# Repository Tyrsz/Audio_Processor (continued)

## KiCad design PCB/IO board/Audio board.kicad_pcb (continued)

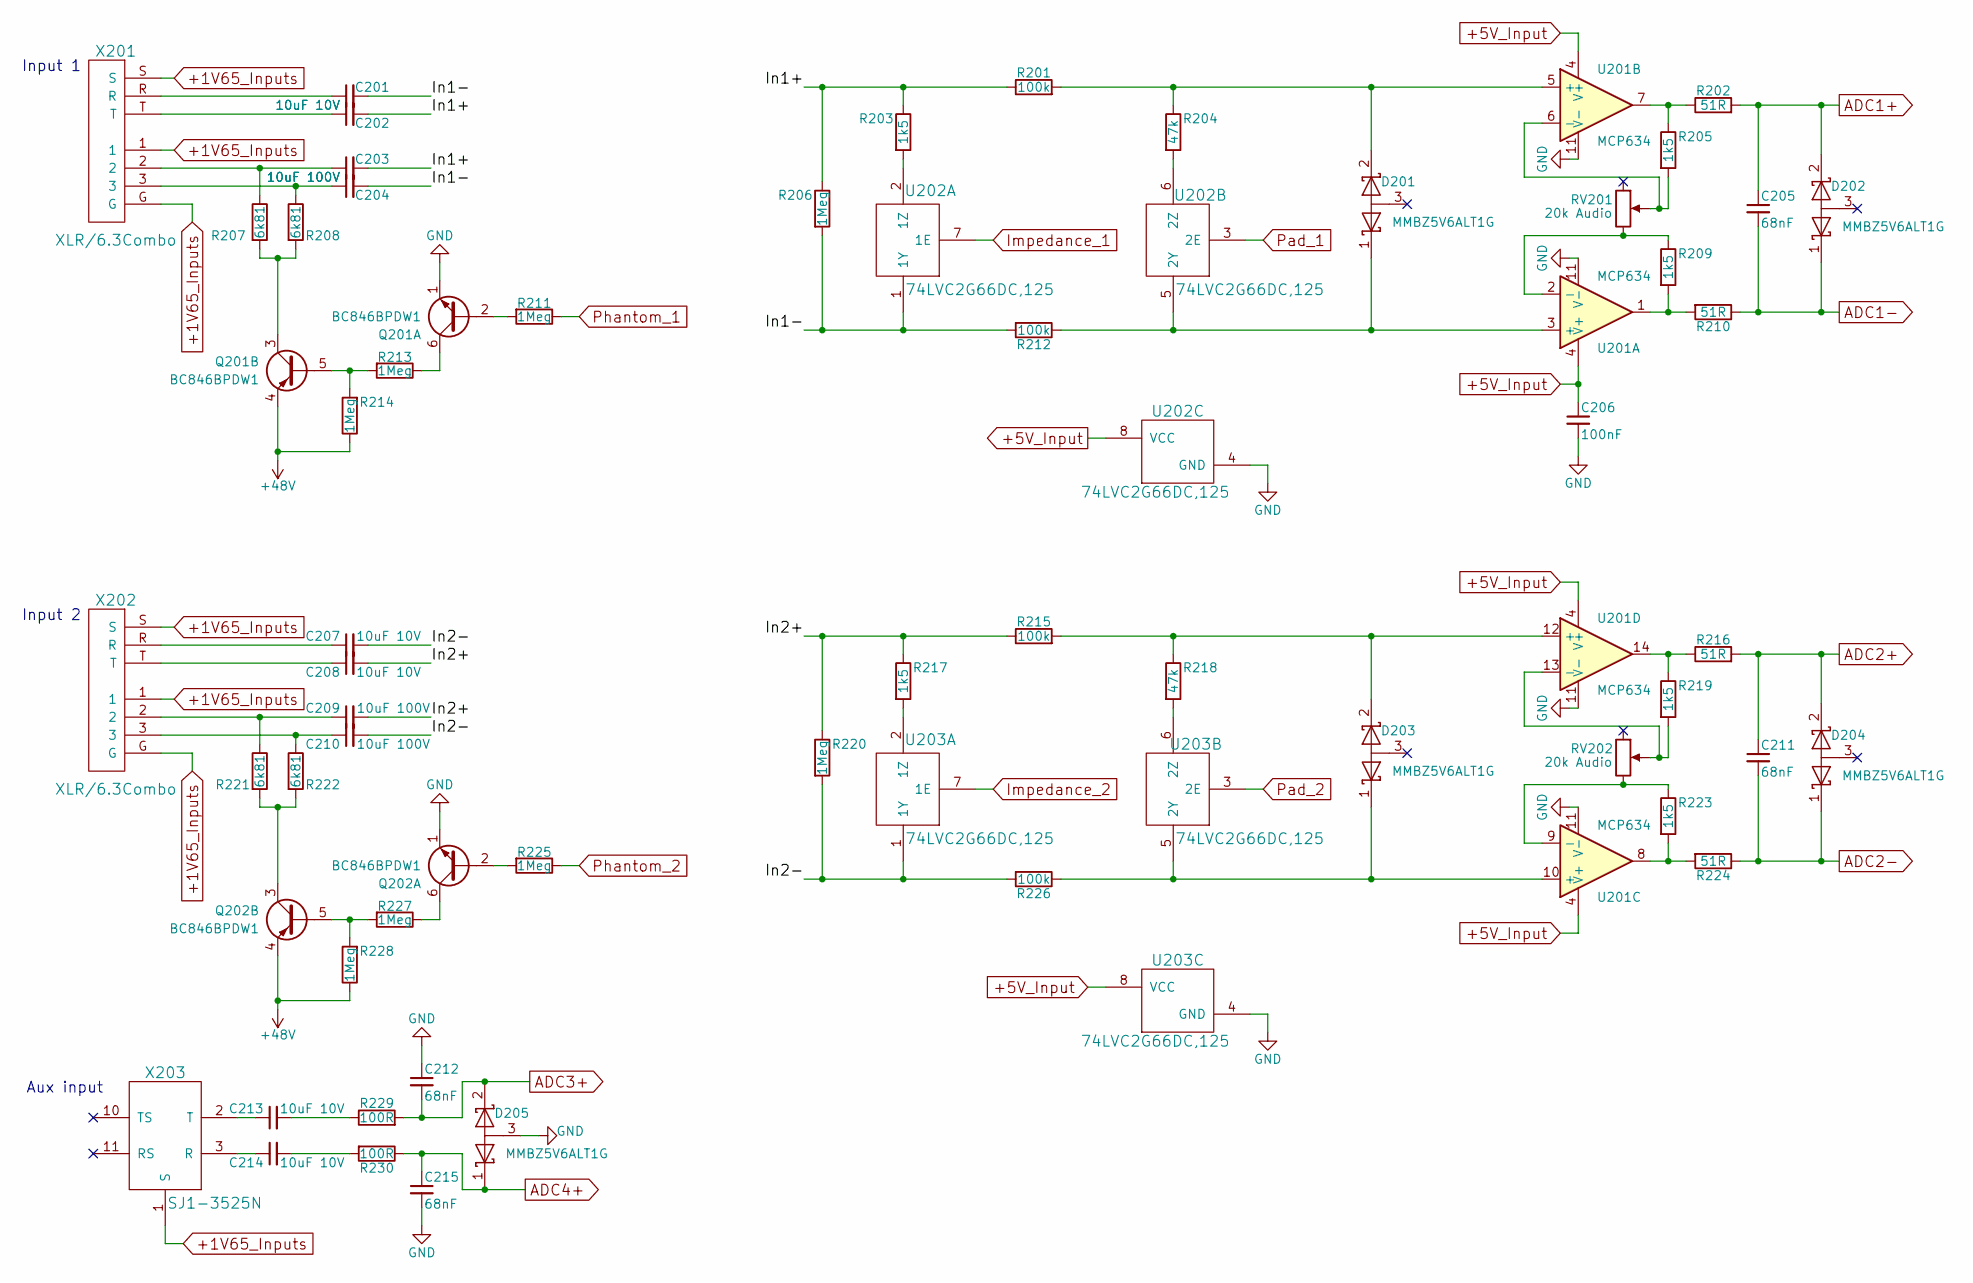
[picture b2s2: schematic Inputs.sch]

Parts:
C201, C202, C207, C208, C213, C214: 10uF 10V; CP_Elec_4x5.3
C203, C204, C209, C210: 10uF 100V; CP_Radial_D8.0mm_P3.50mm
C205, C211, C212, C215: 68nF; C_Rect_L7.5mm_W6.5mm_P5.00mm
C206: 100nF; C_0603
D201, D202, D203, D204, D205: MMBZ5V6ALT1G; SOT-23
Q201, Q202: BC846BPDW1; SOT-363_SC-70-6_Handsoldering
R201, R212, R215, R226: 100k; R_0603
R202, R210, R216, R224: 51R; R_0603
R203, R205, R209, R217, R219, R223: 1k5; R_0603
R204, R218: 47k; R_0603
R206, R211, R213, R214, R220, R225, R227, R228: 1Meg; R_0603
R207, R208, R221, R222: 6k81; R_0603
R229, R230: 100R; R_0603
RV201, RV202: 20k Audio; P140KH1
U201: MCP634; TSSOP-14_4.4x5mm_Pitch0.65mm
U202, U203: 74LVC2G66DC,125; VSSOP-8_2.4x2.1mm_Pitch0.5mm
X201, X202: XLR/6.3Combo; NCJ6FA-H-0
X203: SJ1-3525N; SJ1-352xN

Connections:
+1V65_Inputs: X201.1, X201.G, X201.S, X202.1, X202.G, X202.S, X203.1 (S); also elsewhere on the board
+5V_Input: C206.1, U201.4 (V+), U202.8 (VCC), U203.8 (VCC); also elsewhere on the board
+48V: Q201.4 (E2), Q202.4 (E2), R214.1, R228.1; also elsewhere on the board
/Inputs/In1+: C202.2, C203.2, R201.1, R203.1, R206.1
/Inputs/In1-: C201.2, C204.2, R206.2, R212.2, U202.1 (1Y)
/Inputs/In2+: C208.2, C209.2, R215.1, R217.1, R220.1
/Inputs/In2-: C207.2, C210.2, R220.2, R226.2, U203.1 (1Y)
ADC1+: C205.1, D202.2 (K), R202.2; also elsewhere on the board
ADC1-: C205.2, D202.1 (K), R210.1; also elsewhere on the board
ADC2+: C211.1, D204.2 (K), R216.2; also elsewhere on the board
ADC2-: C211.2, D204.1 (K), R224.1; also elsewhere on the board
ADC3+: C212.2, D205.2 (K), R229.2; also elsewhere on the board
ADC4+: C215.1, D205.1 (K), R230.1; also elsewhere on the board
GND: C206.2, C212.1, C215.2, D205.3 (A), Q201.1 (E1), Q202.1 (E1), U201.11 (V-), U202.4 (GND), U203.4 (GND); also elsewhere on the board
Impedance_1: U202.7 (1E); also elsewhere on the board
Impedance_2: U203.7 (1E); also elsewhere on the board
unnamed: C201.1, X201.R
unnamed: C202.1, X201.T
unnamed: C203.1, R207.1, X201.2
unnamed: C204.1, R208.1, X201.3
unnamed: C207.1, X202.R
unnamed: C208.1, X202.T
unnamed: C209.1, R221.1, X202.2
unnamed: C210.1, R222.1, X202.3
unnamed: C213.1, X203.2 (T)
unnamed: C213.2, R229.1
unnamed: C214.1, X203.3 (R)
unnamed: C214.2, R230.2
unnamed: D201.1 (K), R212.1, U201.3 (+), U202.5 (2Y)
unnamed: D201.2 (K), R201.2, R204.1, U201.5 (+)
unnamed: D203.1 (K), R226.1, U201.10 (+), U203.5 (2Y)
unnamed: D203.2 (K), R215.2, R218.1, U201.12 (+)
unnamed: Q201.2 (B1), R211.2
unnamed: Q201.3 (C2), R207.2, R208.2
unnamed: Q201.5 (B2), R213.2, R214.2
unnamed: Q201.6 (C1), R213.1
unnamed: Q202.2 (B1), R225.2
unnamed: Q202.3 (C2), R221.2, R222.2
unnamed: Q202.5 (B2), R227.2, R228.2
unnamed: Q202.6 (C1), R227.1
unnamed: R202.1, R205.1, U201.7
unnamed: R203.2, U202.2 (1Z)
unnamed: R204.2, U202.6 (2Z)
unnamed: R205.2, RV201.2, U201.6 (-)
unnamed: R209.1, RV201.3, U201.2 (-)
unnamed: R209.2, R210.2, U201.1
unnamed: R216.1, R219.1, U201.14
unnamed: R217.2, U203.2 (1Z)
unnamed: R218.2, U203.6 (2Z)
unnamed: R219.2, RV202.2, U201.13 (-)
unnamed: R223.1, RV202.3, U201.9 (-)
unnamed: R223.2, R224.2, U201.8
Pad_1: U202.3 (2E); also elsewhere on the board
Pad_2: U203.3 (2E); also elsewhere on the board
Phantom_1: R211.1; also elsewhere on the board
Phantom_2: R225.1; also elsewhere on the board

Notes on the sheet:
Aux input
Input 2
Input 1

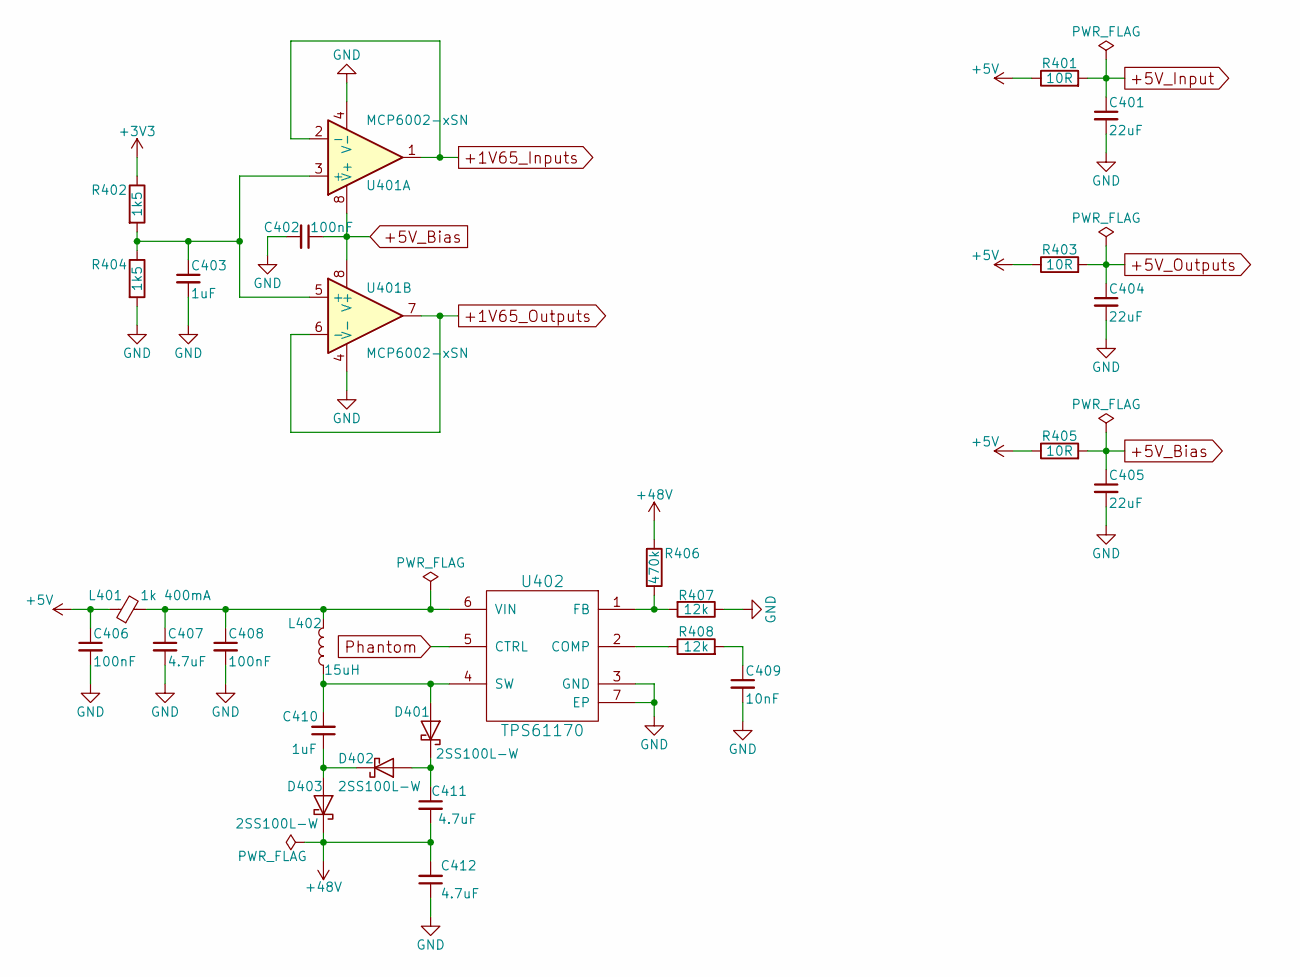
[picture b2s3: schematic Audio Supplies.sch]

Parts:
C401, C404, C405: 22uF; C_0805
C402, C406, C408: 100nF; C_0603
C403: 1uF; C_0603
C407, C411, C412: 4.7uF; C_0805
C409: 10nF; C_0603
C410: 1uF; C_1206
D401, D402, D403: 2SS100L-W; D_SOD-123F
L401: 1k 400mA; L_0603
L402: 15uH; L_0805
R401, R403, R405: 10R; R_0805
R402, R404: 1k5; R_0603
R406: 470k; R_0603
R407, R408: 12k; R_0603
U401: MCP6002-xSN; SOIC-8_3.9x4.9mm_Pitch1.27mm
U402: TPS61170; DFN-6-1EP_2x2mm_Pitch0.65mm

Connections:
+1V65_Inputs: U401.1, U401.2 (-); also elsewhere on the board
+1V65_Outputs: U401.6 (-), U401.7; also elsewhere on the board
+3V3: R402.1; also elsewhere on the board
+5V: C406.1, L401.1, R401.1, R403.1, R405.1; also elsewhere on the board
+5V_Bias: C402.1, C405.1, R405.2, U401.8 (V+)
+5V_Input: C401.1, R401.2; also elsewhere on the board
+5V_Outputs: C404.1, R403.2; also elsewhere on the board
+48V: C411.2, C412.2, D403.1 (K), R406.1; also elsewhere on the board
GND: C401.2, C402.2, C403.2, C404.2, C405.2, C406.2, C407.2, C408.2, C409.2, C412.1, R404.2, R407.1, U401.4 (V-), U402.3 (GND), U402.7 (EP); also elsewhere on the board
unnamed: C403.1, R402.2, R404.1, U401.3 (+), U401.5 (+)
unnamed: C407.1, C408.1, L401.2, L402.2, U402.6 (VIN)
unnamed: C409.1, R408.2
unnamed: C410.1, D402.1 (K), D403.2 (A)
unnamed: C410.2, D401.2 (A), L402.1, U402.4 (SW)
unnamed: C411.1, D401.1 (K), D402.2 (A)
unnamed: R406.2, R407.2, U402.1 (FB)
unnamed: R408.1, U402.2 (COMP)
Phantom: U402.5 (CTRL); also elsewhere on the board

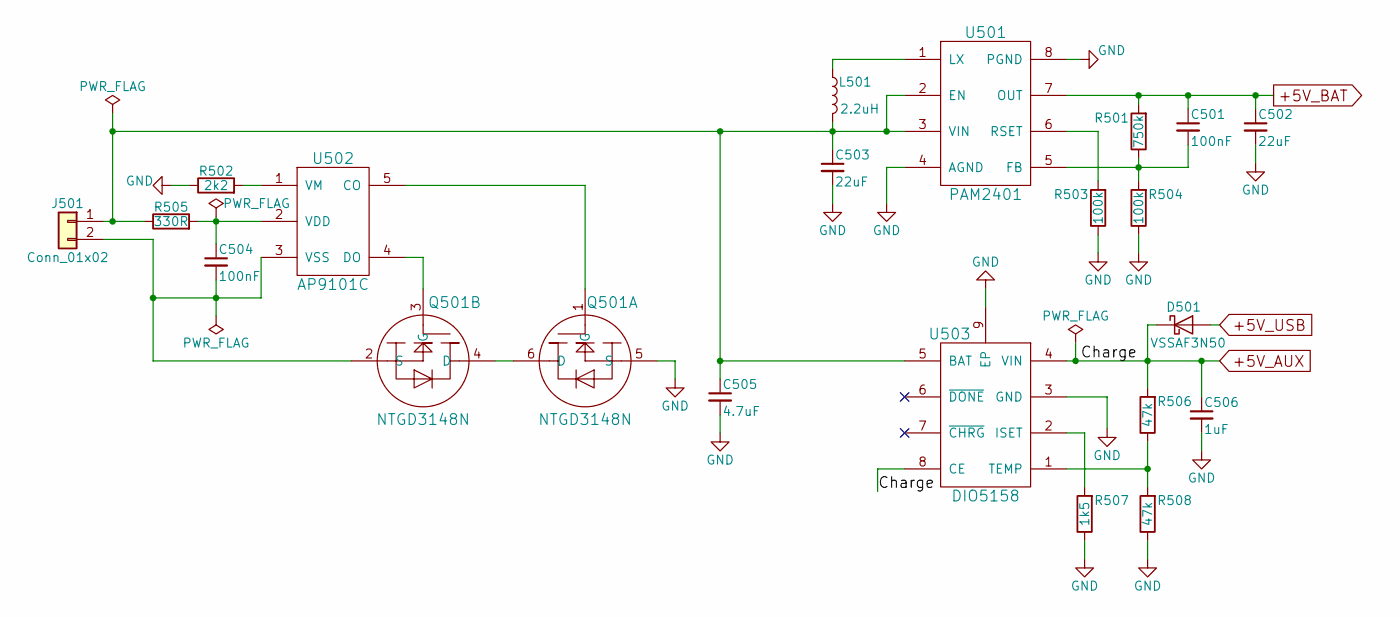
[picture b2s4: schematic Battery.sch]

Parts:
C501, C504: 100nF; C_0603
C502, C503: 22uF; C_0805
C505: 4.7uF; C_0805
C506: 1uF; C_0603
D501: VSSAF3N50; D_SMA
J501: Conn_01x02; Phoenix_1751765
L501: 2.2uH; L-1008
Q501: NTGD3148N; TSOP-6_1.65x3.05mm_Pitch0.95mm
R501: 750k; R_0603
R502: 2k2; R_0603
R503, R504: 100k; R_0603
R505: 330R; R_0603
R506, R508: 47k; R_0603
R507: 1k5; R_0603
U501: PAM2401; MSOP-8_3x3mm_Pitch0.65mm
U502: AP9101C; SOT-23-5
U503: DIO5158; MSOP-8-1EP_3x3mm_Pitch0.65mm

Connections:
+5V_AUX: C506.1, D501.1 (K), R506.2, U503.4 (VIN), U503.8 (CE); also elsewhere on the board
+5V_BAT: C501.1, C502.1, R501.2, U501.7 (OUT); also elsewhere on the board
+5V_USB: D501.2 (A); also elsewhere on the board
GND: C502.2, C503.2, C505.2, C506.2, Q501.5 (S), R502.1, R503.1, R504.1, R507.1, R508.1, U501.4 (AGND), U501.8 (PGND), U503.3 (GND), U503.9 (EP); also elsewhere on the board
unnamed: C501.2, R501.1, R504.2, U501.5 (FB)
unnamed: C503.1, C505.1, J501.1, L501.2, R505.1, U501.2 (EN), U501.3 (VIN), U503.5 (BAT)
unnamed: C504.1, R505.2, U502.2 (VDD)
unnamed: C504.2, J501.2, Q501.2 (S), U502.3 (VSS)
unnamed: L501.1, U501.1 (LX)
unnamed: Q501.1 (G), U502.5 (CO)
unnamed: Q501.3 (G), U502.4 (DO)
unnamed: Q501.4 (D), Q501.6 (D)
unnamed: R502.2, U502.1 (VM)
unnamed: R503.2, U501.6 (RSET)
unnamed: R506.1, R508.2, U503.1 (TEMP)
unnamed: R507.2, U503.2 (ISET)

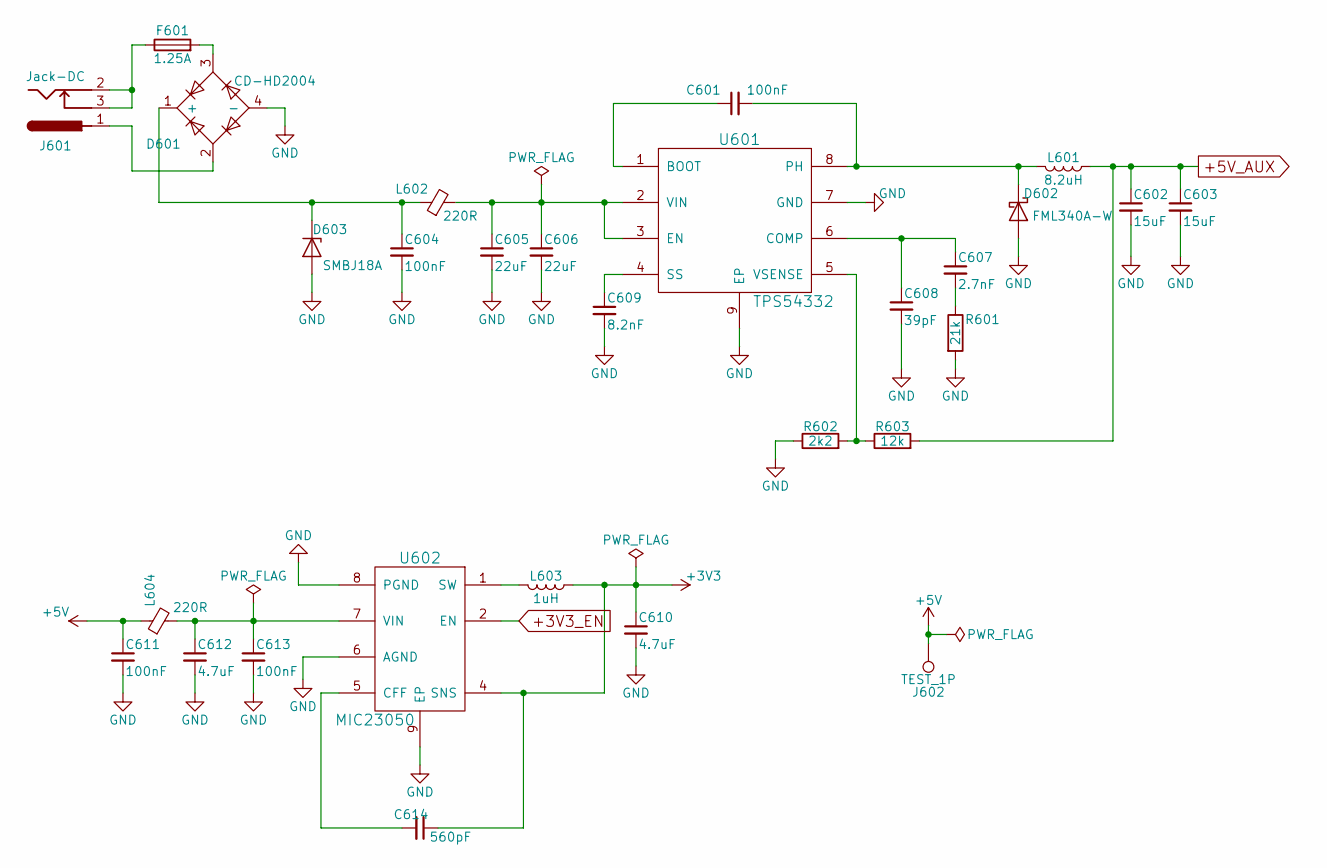
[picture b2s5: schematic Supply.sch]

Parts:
C601, C604, C611, C613: 100nF; C_0603
C602, C603: 15uF; C_0603
C605, C606: 22uF; C_1210
C607: 2.7nF; C_0603
C608: 39pF; C_0603
C609: 8.2nF; C_0603
C610, C612: 4.7uF; C_0805
C614: 560pF; C_0603
D601: CD-HD2004; SMD-4
D602: FML340A-W; D_SMA
D603: SMBJ18A; D_SMB
F601: 1.25A; R_0603
J601: Jack-DC; BARREL_JACK
J602: TEST_1P; Mill-Max_0990
L601: 8.2uH; L_Taiyo-Yuden_NR-60xx_HandSoldering
L602, L604: 220R; L_0603
L603: 1uH; L_0805
R601: 21k; R_0603
R602: 2k2; R_0603
R603: 12k; R_0603
U601: TPS54332; TI_SO-PowerPAD-8_ThermalVias
U602: MIC23050; DFN-8-1EP_2x2mm_Pitch0.5mm

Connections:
+3V3: C610.1, C614.1, L603.1, U602.4 (SNS); also elsewhere on the board
+3V3_EN: U602.2 (EN); also elsewhere on the board
+5V: C611.1, J602.1, L604.1; also elsewhere on the board
+5V_AUX: C602.1, C603.1, L601.1, R603.2; also elsewhere on the board
GND: C602.2, C603.2, C604.2, C605.2, C606.2, C608.2, C609.2, C610.2, C611.2, C612.2, C613.2, D601.4 (-), D602.2 (A), D603.2 (A), R601.2, R602.1, U601.7 (GND), U601.9 (EP), U602.6 (AGND), U602.8 (PGND), U602.9 (EP); also elsewhere on the board
unnamed: C601.1, U601.1 (BOOT)
unnamed: C601.2, D602.1 (K), L601.2, U601.8 (PH)
unnamed: C604.1, D601.1 (+), D603.1 (K), L602.1
unnamed: C605.1, C606.1, L602.2, U601.2 (VIN), U601.3 (EN)
unnamed: C607.1, C608.1, U601.6 (COMP)
unnamed: C607.2, R601.1
unnamed: C609.1, U601.4 (SS)
unnamed: C612.1, C613.1, L604.2, U602.7 (VIN)
unnamed: C614.2, U602.5 (CFF)
unnamed: D601.2, J601.1
unnamed: D601.3, F601.2
unnamed: F601.1, J601.2, J601.3
unnamed: L603.2, U602.1 (SW)
unnamed: R602.2, R603.1, U601.5 (VSENSE)

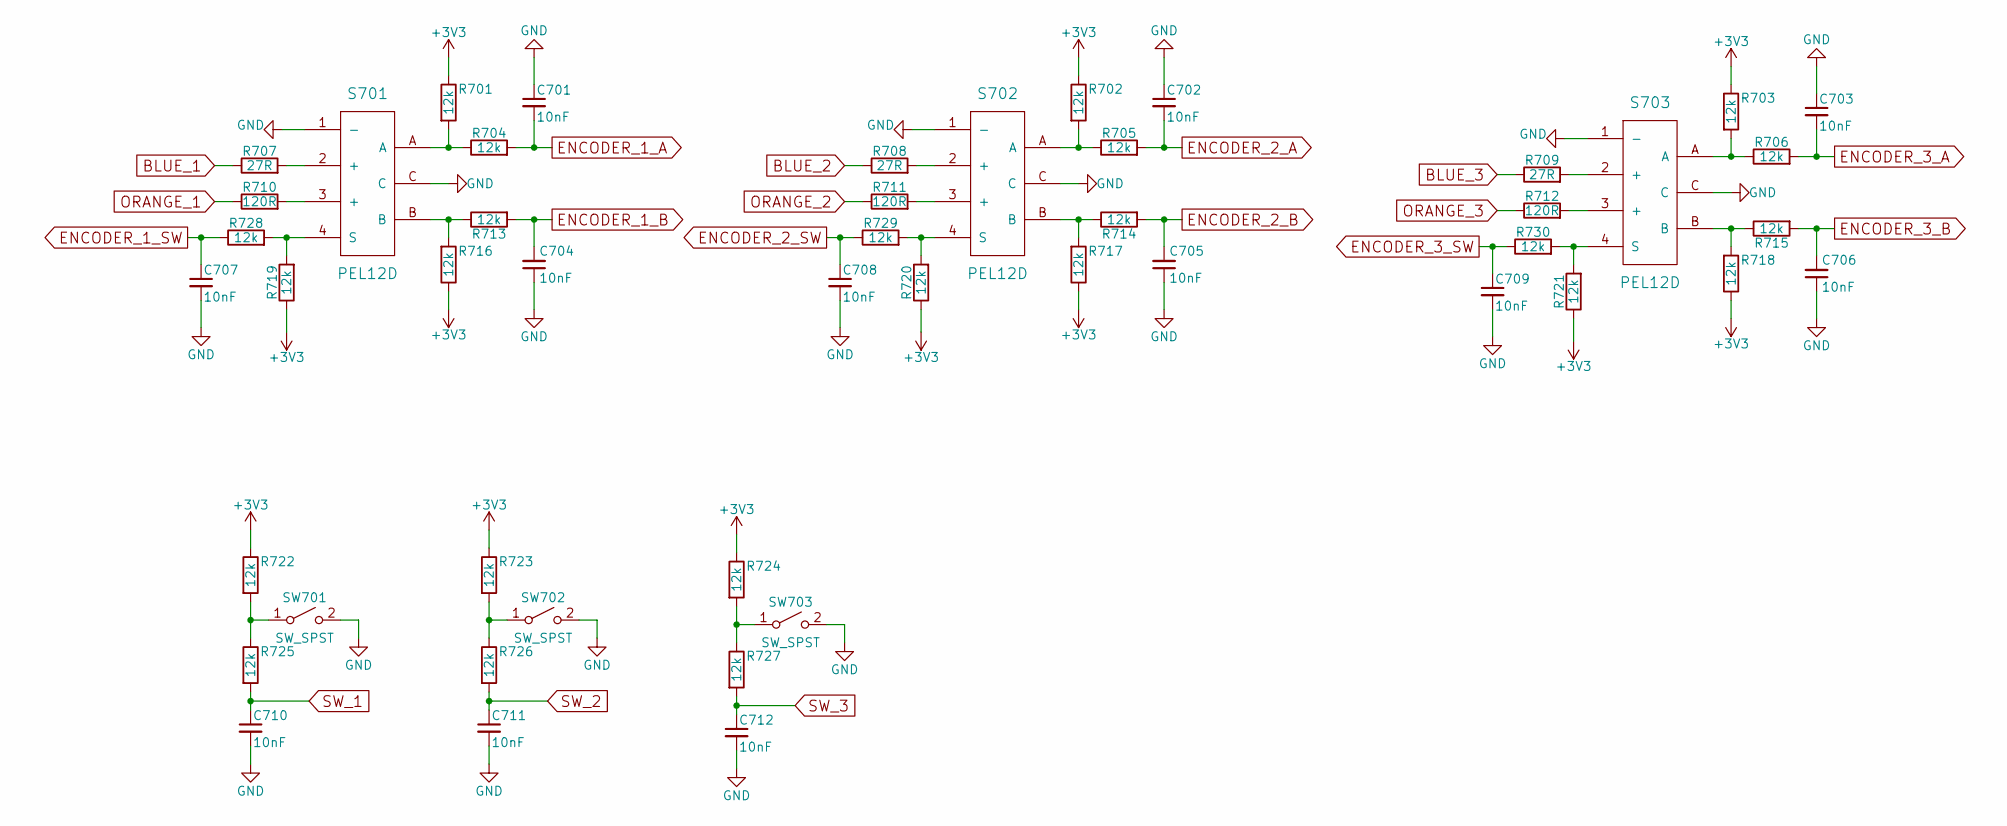
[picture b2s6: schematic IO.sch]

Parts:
C701, C702, C703, C704, C705, C706, C707, C708, C709, C710, C711, C712: 10nF; C_0603
R701, R702, R703, R704, R705, R706, R713, R714, R715, R716, R717, R718, R719, R720, R721, R722, R723, R724, R725, R726, R727, R728, R729, R730: 12k; R_0603
R707, R708, R709: 27R; R_0603
R710, R711, R712: 120R; R_0603
S701, S702, S703: PEL12D; PEL12D-4xxxS
SW701, SW702, SW703: SW_SPST; PS1024A

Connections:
+3V3: R701.1, R702.1, R703.1, R716.1, R717.1, R718.1, R719.1, R720.1, R721.1, R722.1, R723.1, R724.1; also elsewhere on the board
BLUE_1: R707.1; also elsewhere on the board
BLUE_2: R708.1; also elsewhere on the board
BLUE_3: R709.1; also elsewhere on the board
ENCODER_1_A: C701.2, R704.2; also elsewhere on the board
ENCODER_1_B: C704.2, R713.2; also elsewhere on the board
ENCODER_1_SW: C707.1, R728.1; also elsewhere on the board
ENCODER_2_A: C702.2, R705.2; also elsewhere on the board
ENCODER_2_B: C705.2, R714.2; also elsewhere on the board
ENCODER_2_SW: C708.1, R729.1; also elsewhere on the board
ENCODER_3_A: C703.2, R706.2; also elsewhere on the board
ENCODER_3_B: C706.2, R715.2; also elsewhere on the board
ENCODER_3_SW: C709.1, R730.1; also elsewhere on the board
GND: C701.1, C702.1, C703.1, C704.1, C705.1, C706.1, C707.2, C708.2, C709.2, C710.2, C711.2, C712.2, S701.1 (-), S701.C, S702.1 (-), S702.C, S703.1 (-), S703.C, SW701.2 (B), SW702.2 (B), SW703.2 (B); also elsewhere on the board
unnamed: R701.2, R704.1, S701.A
unnamed: R702.2, R705.1, S702.A
unnamed: R703.2, R706.1, S703.A
unnamed: R707.2, S701.2 (+)
unnamed: R708.2, S702.2 (+)
unnamed: R709.2, S703.2 (+)
unnamed: R710.2, S701.3 (+)
unnamed: R711.2, S702.3 (+)
unnamed: R712.2, S703.3 (+)
unnamed: R713.1, R716.2, S701.B
unnamed: R714.1, R717.2, S702.B
unnamed: R715.1, R718.2, S703.B
unnamed: R719.2, R728.2, S701.4 (S)
unnamed: R720.2, R729.2, S702.4 (S)
unnamed: R721.2, R730.2, S703.4 (S)
unnamed: R722.2, R725.1, SW701.1 (A)
unnamed: R723.2, R726.1, SW702.1 (A)
unnamed: R724.2, R727.1, SW703.1 (A)
ORANGE_1: R710.1; also elsewhere on the board
ORANGE_2: R711.1; also elsewhere on the board
ORANGE_3: R712.1; also elsewhere on the board
SW_1: C710.1, R725.2; also elsewhere on the board
SW_2: C711.1, R726.2; also elsewhere on the board
SW_3: C712.1, R727.2; also elsewhere on the board

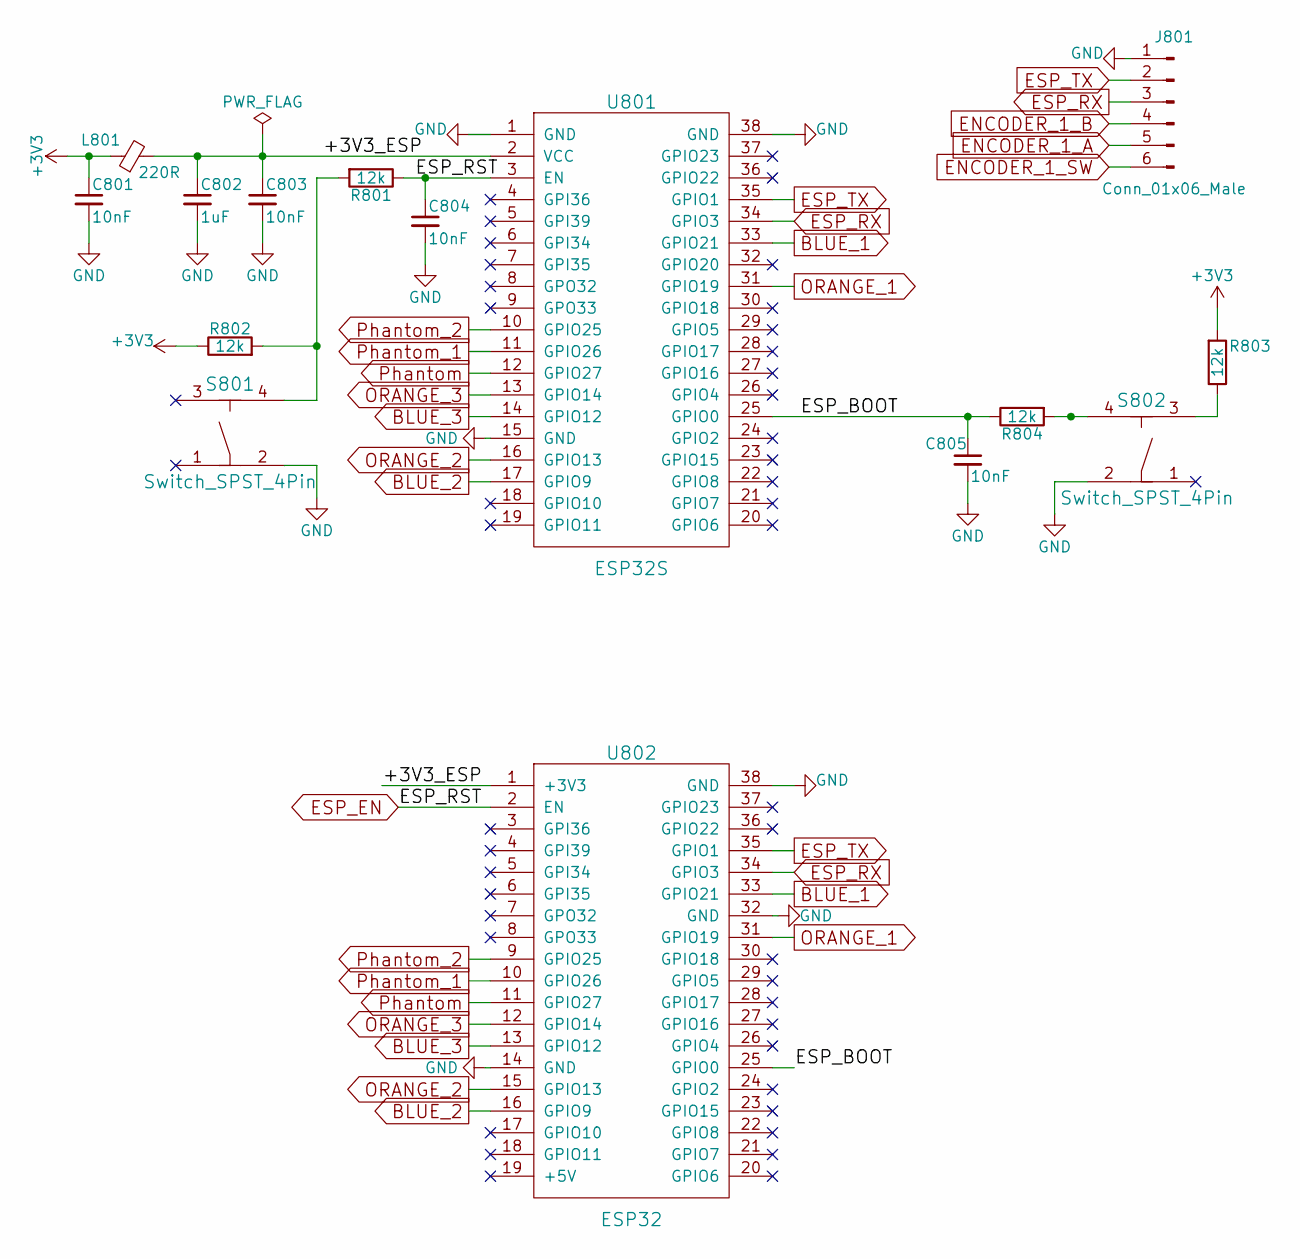
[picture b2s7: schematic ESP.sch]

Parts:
C801, C803, C804, C805: 10nF; C_0603
C802: 1uF; C_0603
J801: Conn_01x06_Male; Pin_Header_Straight_1x06_Pitch2.54mm_SMD_Pin1Right
L801: 220R; L_0603_HandSoldering
R801, R802, R803, R804: 12k; R_0603
S801, S802: Switch_SPST_4Pin; FSM4JSMATR
U801: ESP32S
U802: ESP32

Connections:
+3V3: C801.1, L801.1, R802.1, R803.2; also elsewhere on the board
/ESP/+3V3_ESP: C802.1, C803.1, L801.2, U801.2 (VCC), U802.1 (+3V3)
/ESP/ESP_BOOT: C805.1, R804.1, U801.25 (GPIO0), U802.25 (GPIO0)
BLUE_1: U801.33 (GPIO21), U802.33 (GPIO21); also elsewhere on the board
BLUE_2: U801.17 (GPIO9), U802.16 (GPIO9); also elsewhere on the board
BLUE_3: U801.14 (GPIO12), U802.13 (GPIO12); also elsewhere on the board
ENCODER_1_A: J801.5; also elsewhere on the board
ENCODER_1_B: J801.4; also elsewhere on the board
ENCODER_1_SW: J801.6; also elsewhere on the board
ESP_EN: C804.1, R801.1, U801.3 (EN), U802.2 (EN); also elsewhere on the board
ESP_RX: J801.3, U801.34 (GPIO3), U802.34 (GPIO3); also elsewhere on the board
ESP_TX: J801.2, U801.35 (GPIO1), U802.35 (GPIO1); also elsewhere on the board
GND: C801.2, C802.2, C803.2, C804.2, C805.2, J801.1, S801.2, S802.2, U801.1 (GND), U801.15 (GND), U801.38 (GND), U802.14 (GND), U802.32 (GND), U802.38 (GND); also elsewhere on the board
unnamed: R801.2, R802.2, S801.4
unnamed: R803.1, S802.3
unnamed: R804.2, S802.4
ORANGE_1: U801.31 (GPIO19), U802.31 (GPIO19); also elsewhere on the board
ORANGE_2: U801.16 (GPIO13), U802.15 (GPIO13); also elsewhere on the board
ORANGE_3: U801.13 (GPIO14), U802.12 (GPIO14); also elsewhere on the board
Phantom: U801.12 (GPIO27), U802.11 (GPIO27); also elsewhere on the board
Phantom_1: U801.11 (GPIO26), U802.10 (GPIO26); also elsewhere on the board
Phantom_2: U801.10 (GPIO25), U802.9 (GPIO25); also elsewhere on the board

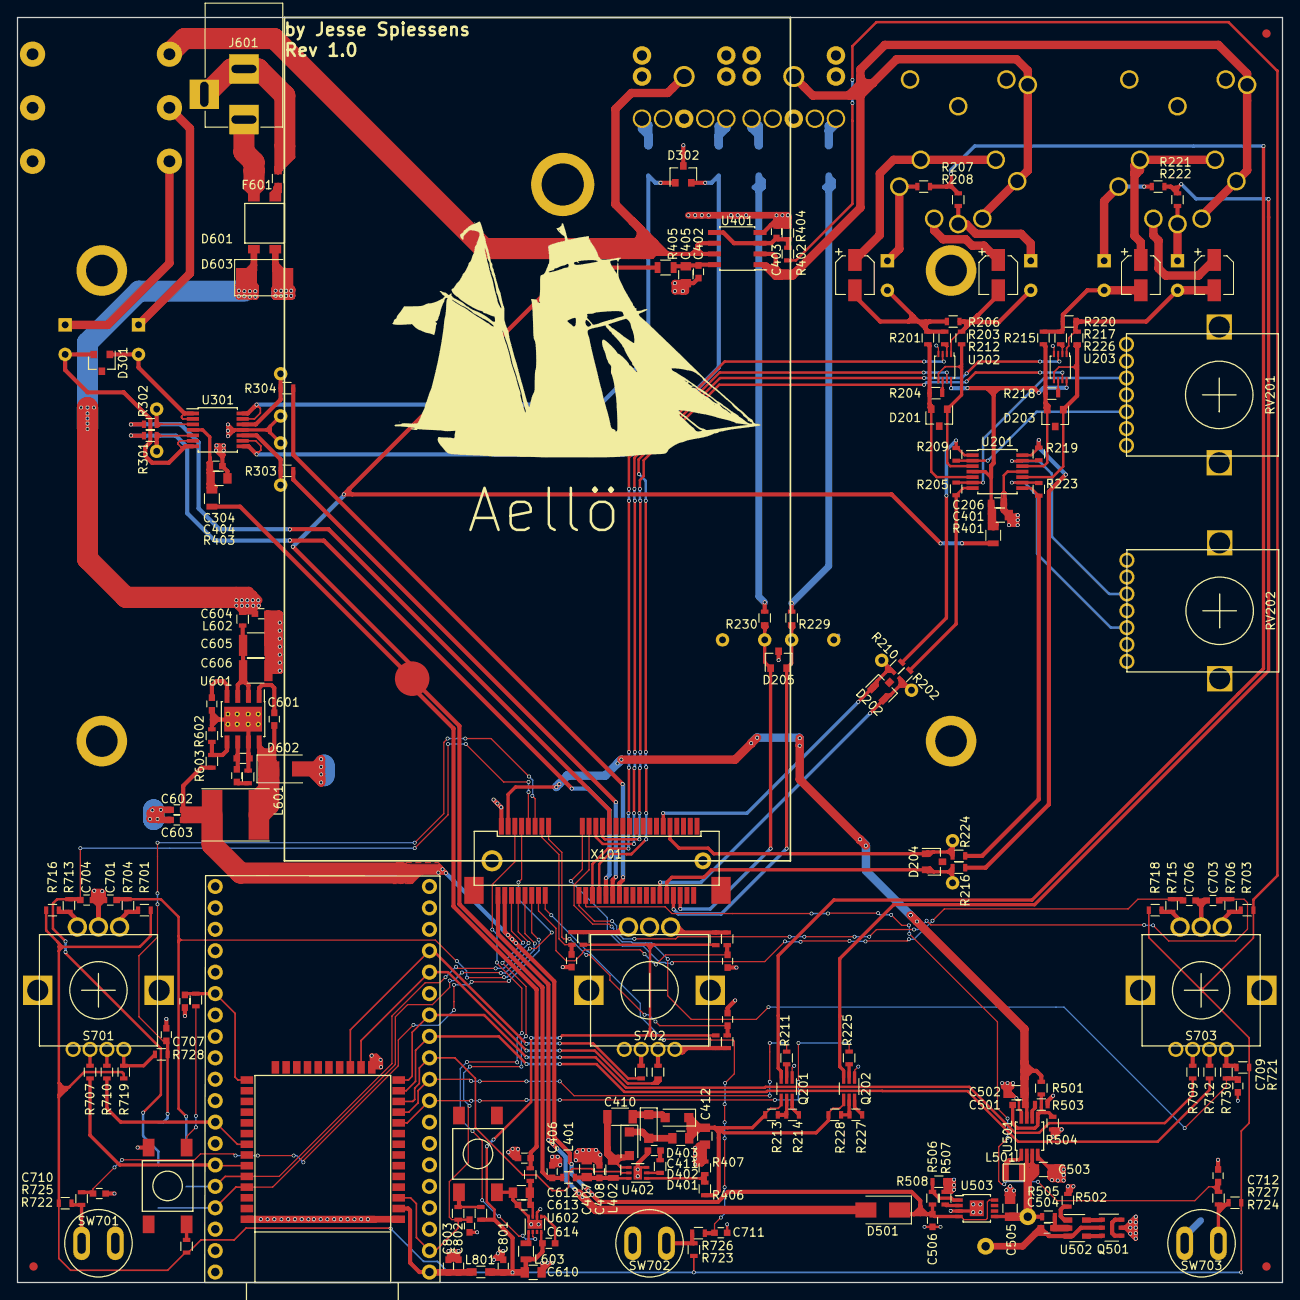
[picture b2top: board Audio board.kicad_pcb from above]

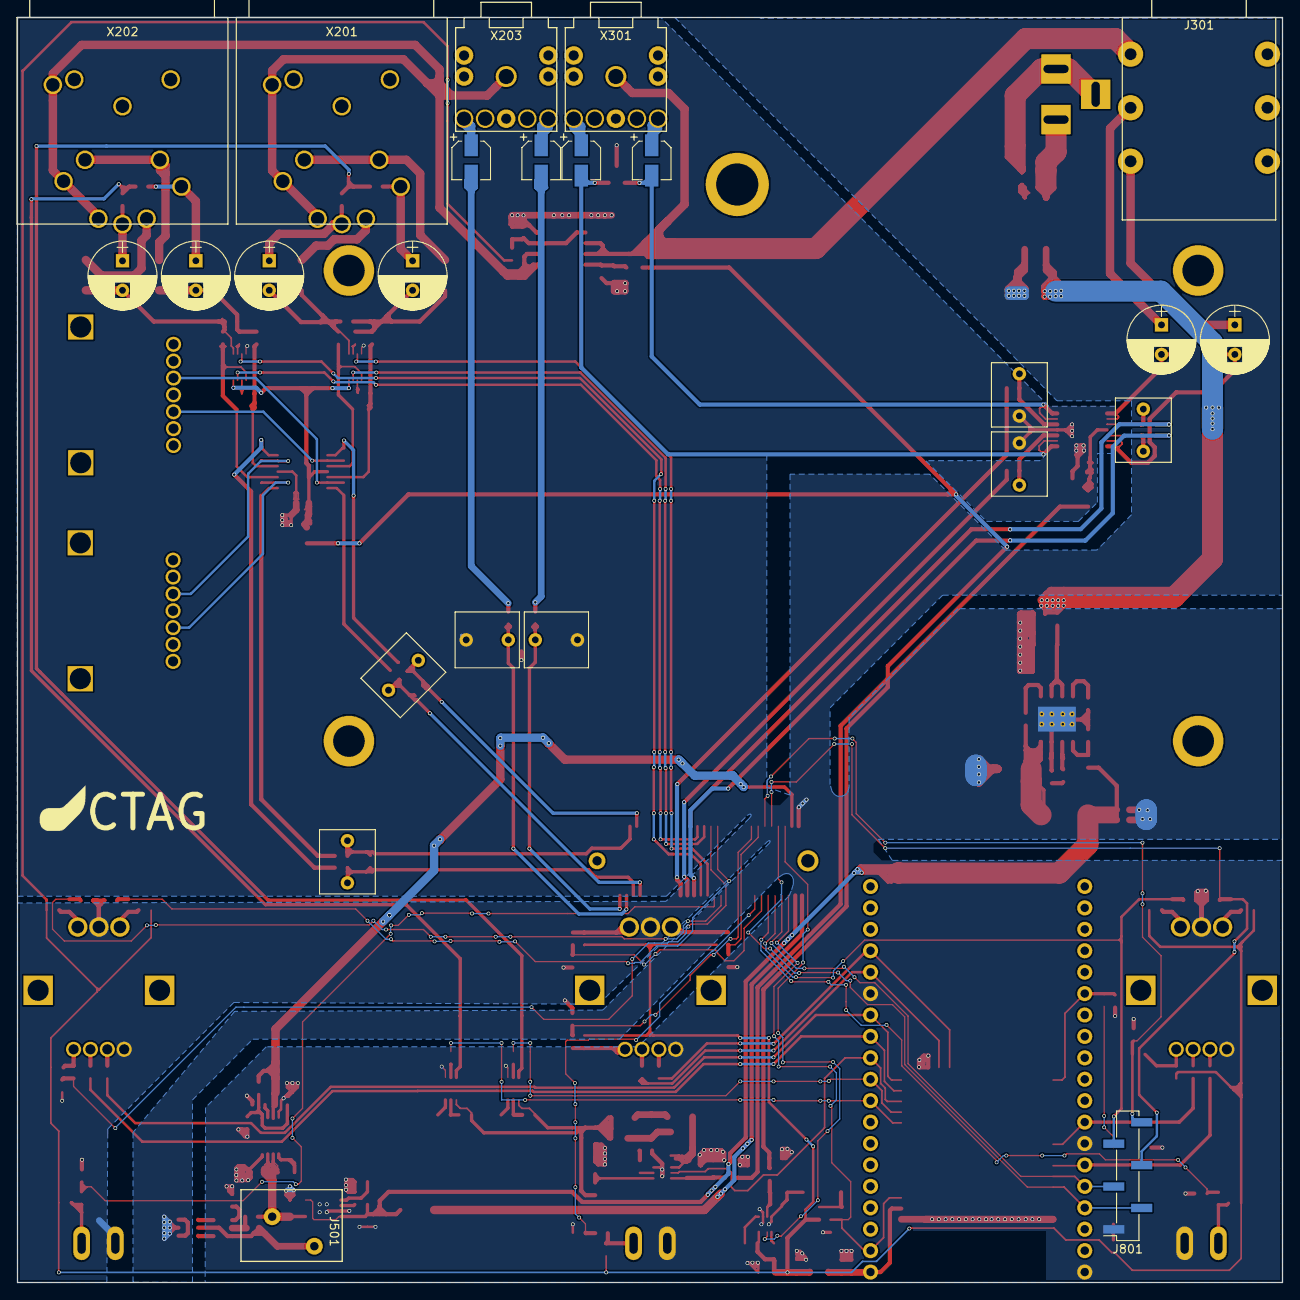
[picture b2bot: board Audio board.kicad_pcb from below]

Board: 2 copper layers, 150.0 x 150.0 mm, 223 parts (24 on the bottom side), 160 nets.

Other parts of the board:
C301, C303: 10uF 100V; CP_Radial_D8.0mm_P3.50mm
C302, C306, C307: 68nF; C_Rect_L7.5mm_W6.5mm_P5.00mm
C304: 100nF; C_0603
C305, C308: 10uF 10V; CP_Elec_4x5.3
D301, D302: MMBZ5V6ALT1G; SOT-23
J301: 6.3mm TRS; NMJ6HFD2-NW
R301, R302: 51R; R_0603
R303, R304: 100R; R_0603
U301: TLV9064; TSSOP-14_4.4x5mm_Pitch0.65mm
X301: SJ1-3525N; SJ1-352xN

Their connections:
+1V65_Outputs: J301.3, X301.1; also elsewhere on the board
+5V_Outputs: C304.1, U301.4; also elsewhere on the board
DAC1+: R301.1; also elsewhere on the board
DAC1-: R302.2; also elsewhere on the board
DAC2+: R303.1; also elsewhere on the board
DAC3+: R304.2; also elsewhere on the board
GND: C304.2, C306.2, C307.1, D302.3, U301.11; also elsewhere on the board
unnamed: C301.1, J301.1
unnamed: C301.2, D301.2, U301.6, U301.7
unnamed: C302.1, R301.2, U301.5
unnamed: C302.2, R302.1, U301.3
unnamed: C303.1, J301.2
unnamed: C303.2, D301.1, U301.1, U301.2
unnamed: C305.1, X301.2
unnamed: C305.2, D302.2, U301.8, U301.9
unnamed: C306.1, R303.2, U301.10
unnamed: C307.2, R304.1, U301.12
unnamed: C308.1, X301.3
unnamed: C308.2, D302.1, U301.13, U301.14

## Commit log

2018-03-23 :tada: Added .gitattributes & .gitignore files
2018-03-23 Schematics Rev 1
    All schematics done - Revision 1
2018-03-29 Schematics + Footprints Rev.1
    Ready to route.
2018-03-30 Schematics & PCB
    Schematics update - ERC error fixing
    PCB - setup & PCB outline
2018-03-30 Schematic updates + PCB placement
2018-04-01 Component Placement - RN
    All components placed except for RAM Resistor Networks
2018-04-02 RAM Routing - Data
    All RAM routing & matching done, supply still needs to be done
2018-04-03 RAM + Display
    Ram & display routed + matched-ish
2018-04-03 High Speed routing
    High speed routing (USB, SDMMC, CODEC, RAM and Screen) are hooked up
2018-04-04 PCI almost routed
2018-04-05 Almost done routing
    20 connections to be made.
2018-04-05 Routing done Rev 1
    Still need to add some testpoints and art
2018-04-06 Added Testpoints
2018-04-08 Added ground fills & art
2018-04-09 Minor updates keepout
2018-04-10 Gerbers created
2018-04-10 Addedd paste to gerbers
2018-04-18 Audio board project added
2018-04-18 Inputs done
2018-04-19 Schematics without ESP
2018-04-21 Schematics Rev 1.0
2018-04-21 Component Placement - No pul-up
    ALmost finished component placement expect for pull ups and low pass
    filters for switches etc
2018-04-22 PCB Backup
2018-04-23 IO board Rev 1.0 RC-1
    Board for inspection by Supervisor
2018-04-23 Rev 1.0 RC1 gerbers
2018-04-23 IO Rev 1.0 RC2 + Gerbers
    ESP antenna keepout added
2018-05-08 SPI + SDRAM working
    No interrupts
2018-05-11 SPI + Audio working in blocking mode
2018-05-11 TDM Working blocking mod
2018-05-11 Revert "TDM Working blocking mod"
    This reverts commit 89f7c79b6d21f6a7bfbc521e90000ab89b4e23d1.
2018-05-11 TDM working again
2018-05-15 Initial structure
2018-05-18 DMA Working
2018-05-27 Thesis
2019-11-11 FMC_SDRAM working
    Initialised SDRAM
    Access to 32Mbyte in uint32 form.
2019-11-11 SDRAM + Schematic Plot
    fixed typo in FMC_Play
    replotted schematics
2019-11-11 SDRAM restructured
2019-11-11 SDRAM fix + Firmware v1.0 start
    Fixed hardfault in FMC_play
    Made new project using latest HAL and CubeMX
    MCU now runs at 480MHz, RAM at 120MHz
2019-11-17 SAI attempts
    works in blocking mode
    DMA mode only gets one sample, then stops even though it should still be running
